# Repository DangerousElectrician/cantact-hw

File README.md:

I need a sensor node that sits on a CAN bus. This looks like a good place to start.

# CANtact Hardware

This repository contains the hardware design files for the CANtact tool. They 
can be opened and edited with [KiCad](http://www.kicad-pcb.org/).

A PDF of the schematic is available
[here](https://github.com/CANtact/cantact-hw/blob/master/cantact.pdf?raw=true).

## License

Hardware files released under the [Creative Commons Attribution-ShareAlike 4.0
International License](http://creativecommons.org/licenses/by-sa/4.0/) (CC BY-SA
4.0)

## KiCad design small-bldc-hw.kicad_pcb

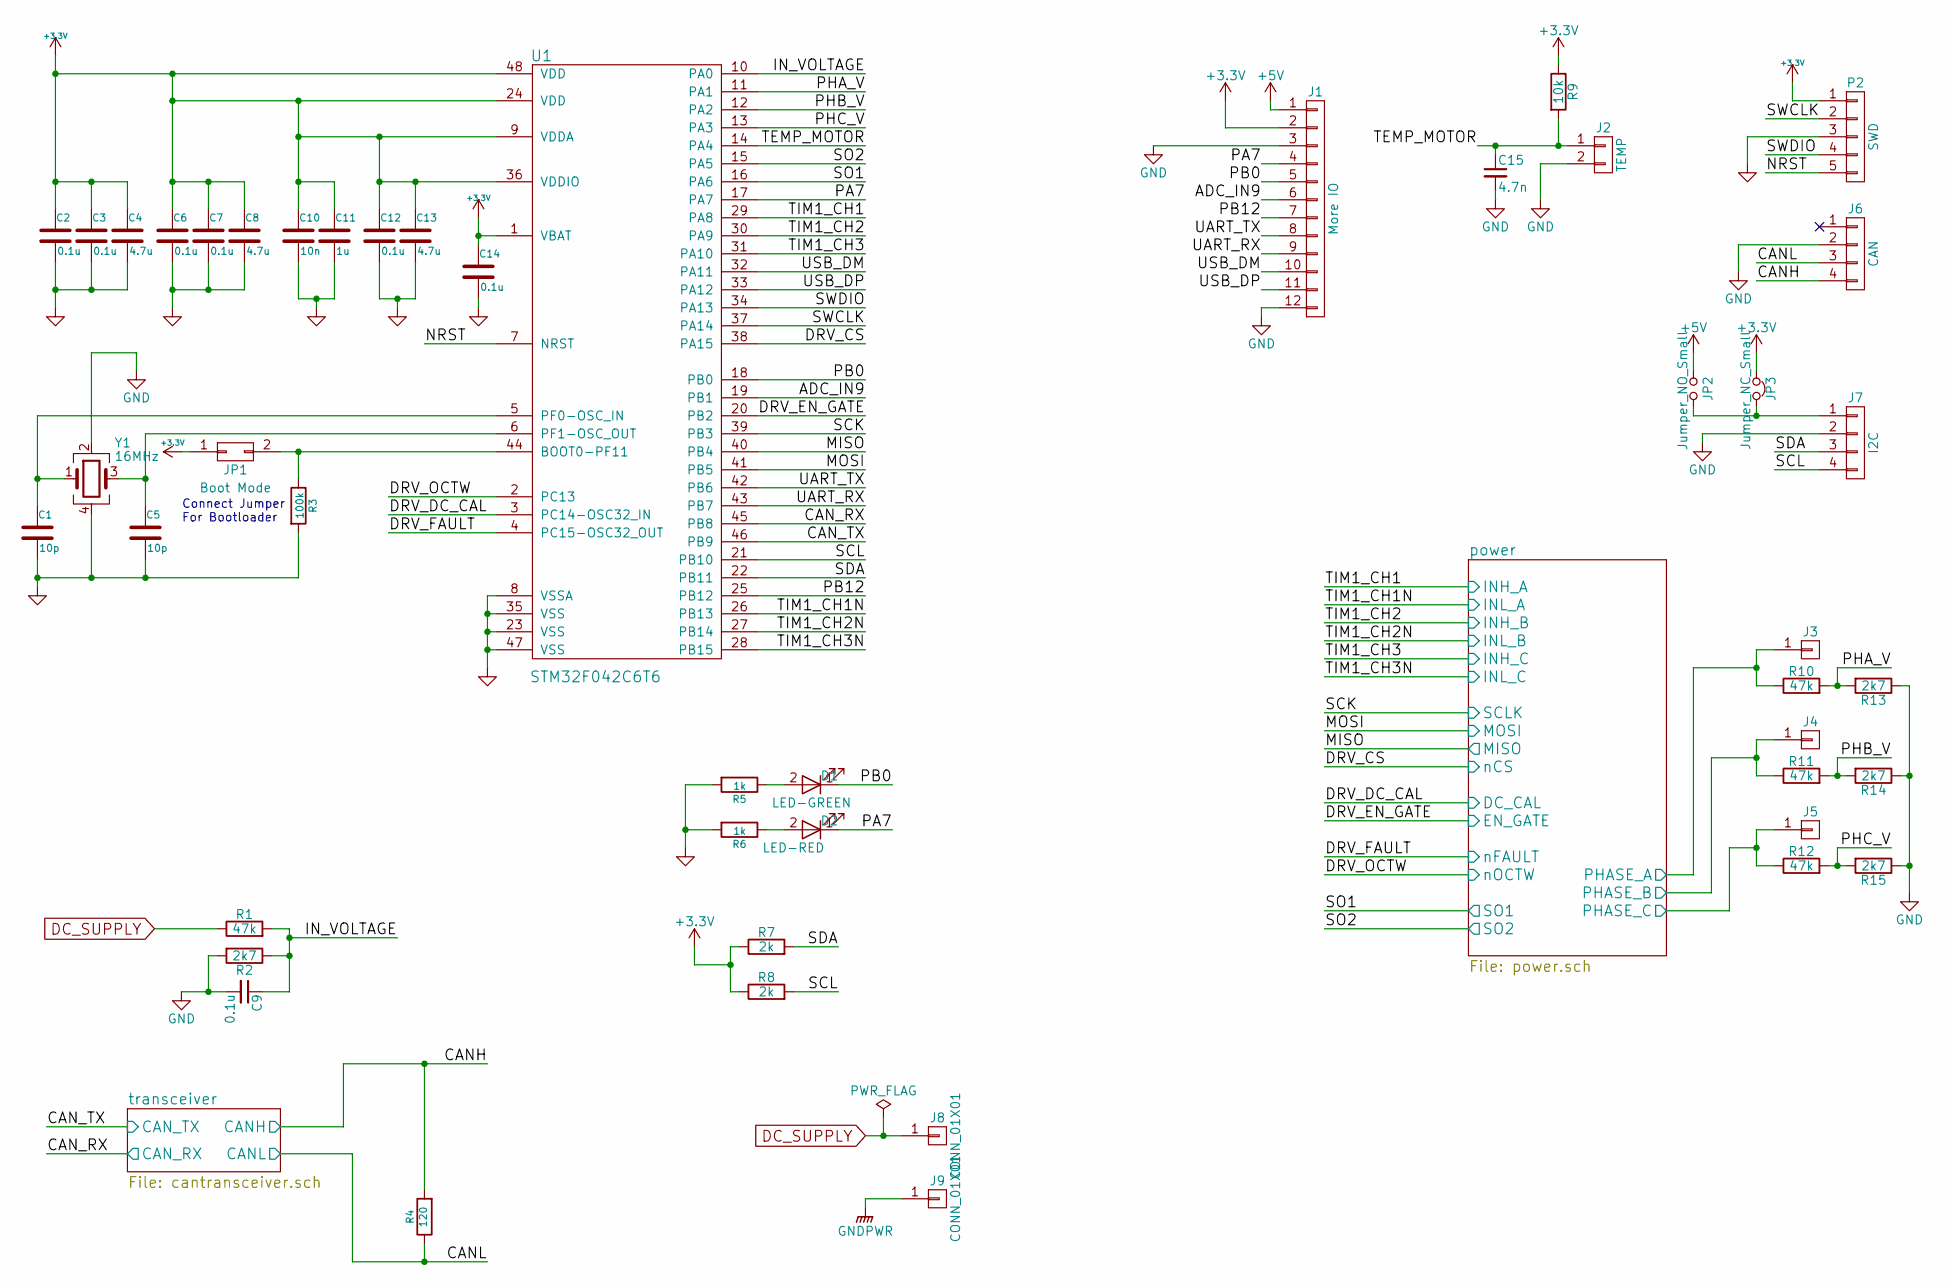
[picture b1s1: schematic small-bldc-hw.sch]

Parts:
C1, C5: 10p; C_0201; MPN GRM0335C1H100JA01D
C2, C9: 0.1u; C_0402; MPN CL05A104KP5NNNC
C3, C6, C7: 0.1u; C_0402; MPN GRM188R71C104KA01D
C4: 4.7u; C_0603; MPN CL10B475KQ8NQNC
C8, C13: 4.7u; C_0603; MPN GRM188R60J475KE19D
C10: 10n; C_0402; MPN GRM188R71H103KA01D
C11: 1u; C_0402; MPN GRM188R61E105KA12D
C12, C14: 0.1u; C_0402; MPN CL05B104KO5NNNC
C15: 4.7n; C_0201; MPN GRM033R71A472KA01D
D1: LED-GREEN; LED_0603; MPN LTST-C191KGKT
D2: LED-RED; LED_0603; MPN LTST-C191KRKT
J1: More IO; JST_SH_SM12B-SRSS-TB_12x1.00mm_Angled
J2: TEMP; JST_SH_SM02B-SRSS-TB_02x1.00mm_Angled
J3, J4, J5, J8, J9: CONN_01X01; SolderWirePad_single_SMD_5x3.5mm_holes
J6: CAN; JST_SH_SM04B-SRSS-TB_04x1.00mm_Angled
J7: I2C; JST_SH_SM04B-SRSS-TB_04x1.00mm_Angled
JP1: Boot Mode; R_0603_HandSoldering
JP2: Jumper_NO_Small; R_0402
JP3: Jumper_NC_Small; R_0402
P2: SWD; JST_SH_SM05B-SRSS-TB_05x1.00mm_Angled
R1, R10, R11, R12: 47k; R_0603
R2, R13, R14, R15: 2k7; R_0201
R3: 100k; R_0201; MPN MCR03ERTF5100
R4: 120; R_0201; MPN MCR03ERTF1200
R5, R6: 1k; R_0201; MPN MCR03ERTF1200
R7, R8: 2k; R_0402
R9: 10k; R_0201
U1: STM32F042C6T6; LQFP-48_7x7mm_Pitch0.5mm; MPN STM32F042C6T6
Y1: 16MHz; Crystal_SMD_3225-4pin_3.2x2.5mm; MPN FA-238 16.0000MB-K3

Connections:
+3V3: C2.1, C3.1, C4.1, C6.1, C7.1, C8.1, C10.1, C11.1, C12.1, C13.1, C14.1, J1.2, JP1.1, JP3.1, P2.1, R7.1, R8.1, R9.1, U1.1 (VBAT), U1.9 (VDDA), U1.24 (VDD), U1.36 (VDDIO), U1.48 (VDD); also elsewhere on the board
+5V: J1.1, JP2.1; also elsewhere on the board
/ADC_IN9: J1.6, U1.19 (PB1)
/CANH: J6.4, R4.2; also elsewhere on the board
/CANL: J6.3, R4.1; also elsewhere on the board
/CAN_RX: U1.45 (PB8); also elsewhere on the board
/CAN_TX: U1.46 (PB9); also elsewhere on the board
/DRV_CS: U1.38 (PA15); also elsewhere on the board
/DRV_DC_CAL: U1.3 (PC14-OSC32_IN); also elsewhere on the board
/DRV_EN_GATE: U1.20 (PB2); also elsewhere on the board
/DRV_FAULT: U1.4 (PC15-OSC32_OUT); also elsewhere on the board
/DRV_OCTW: U1.2 (PC13); also elsewhere on the board
/IN_VOLTAGE: C9.1, R1.2, R2.1, U1.10 (PA0)
/MISO: U1.40 (PB4); also elsewhere on the board
/MOSI: U1.41 (PB5); also elsewhere on the board
/NRST: P2.5, U1.7 (NRST)
/PA7: D2.1 (K), J1.4, U1.17 (PA7)
/PB0: D1.1 (K), J1.5, U1.18 (PB0)
/PB12: J1.7, U1.25 (PB12)
/PHA_V: R10.2, R13.2, U1.11 (PA1)
/PHB_V: R11.2, R14.2, U1.12 (PA2)
/PHC_V: R12.2, R15.2, U1.13 (PA3)
/SCK: U1.39 (PB3); also elsewhere on the board
/SCL: J7.4, R8.2, U1.21 (PB10)
/SDA: J7.3, R7.2, U1.22 (PB11)
/SO1: U1.16 (PA6); also elsewhere on the board
/SO2: U1.15 (PA5); also elsewhere on the board
/SWCLK: P2.2, U1.37 (PA14)
/SWDIO: P2.4, U1.34 (PA13)
/TEMP_MOTOR: C15.1, J2.1, R9.2, U1.14 (PA4)
/TIM1_CH1: U1.29 (PA8); also elsewhere on the board
/TIM1_CH1N: U1.26 (PB13); also elsewhere on the board
/TIM1_CH2: U1.30 (PA9); also elsewhere on the board
/TIM1_CH2N: U1.27 (PB14); also elsewhere on the board
/TIM1_CH3: U1.31 (PA10); also elsewhere on the board
/TIM1_CH3N: U1.28 (PB15); also elsewhere on the board
/UART_RX: J1.9, U1.43 (PB7)
/UART_TX: J1.8, U1.42 (PB6)
/USB_DM: J1.10, U1.32 (PA11)
/USB_DP: J1.11, U1.33 (PA12)
/power/PHASE_A: J3.1, R10.1; also elsewhere on the board
/power/PHASE_B: J4.1, R11.1; also elsewhere on the board
/power/PHASE_C: J5.1, R12.1; also elsewhere on the board
DC_SUPPLY: J8.1, R1.1; also elsewhere on the board
GND: C1.2, C2.2, C3.2, C4.2, C5.2, C6.2, C7.2, C8.2, C9.2, C10.2, C11.2, C12.2, C13.2, C14.2, C15.2, J1.3, J1.12, J2.2, J6.2, J7.2, P2.3, R2.2, R3.2, R5.2, R6.2, R13.1, R14.1, R15.1, U1.8 (VSSA), U1.23 (VSS), U1.35 (VSS), U1.47 (VSS), Y1.2, Y1.4; also elsewhere on the board
GNDPWR: J9.1; also elsewhere on the board
unnamed: C1.1, U1.5 (PF0-OSC_IN), Y1.1
unnamed: C5.1, U1.6 (PF1-OSC_OUT), Y1.3
unnamed: D1.2 (A), R5.1
unnamed: D2.2 (A), R6.1
unnamed: J7.1, JP2.2, JP3.2
unnamed: JP1.2, R3.1, U1.44 (BOOT0-PF11)

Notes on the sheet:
Connect Jumper For Bootloader

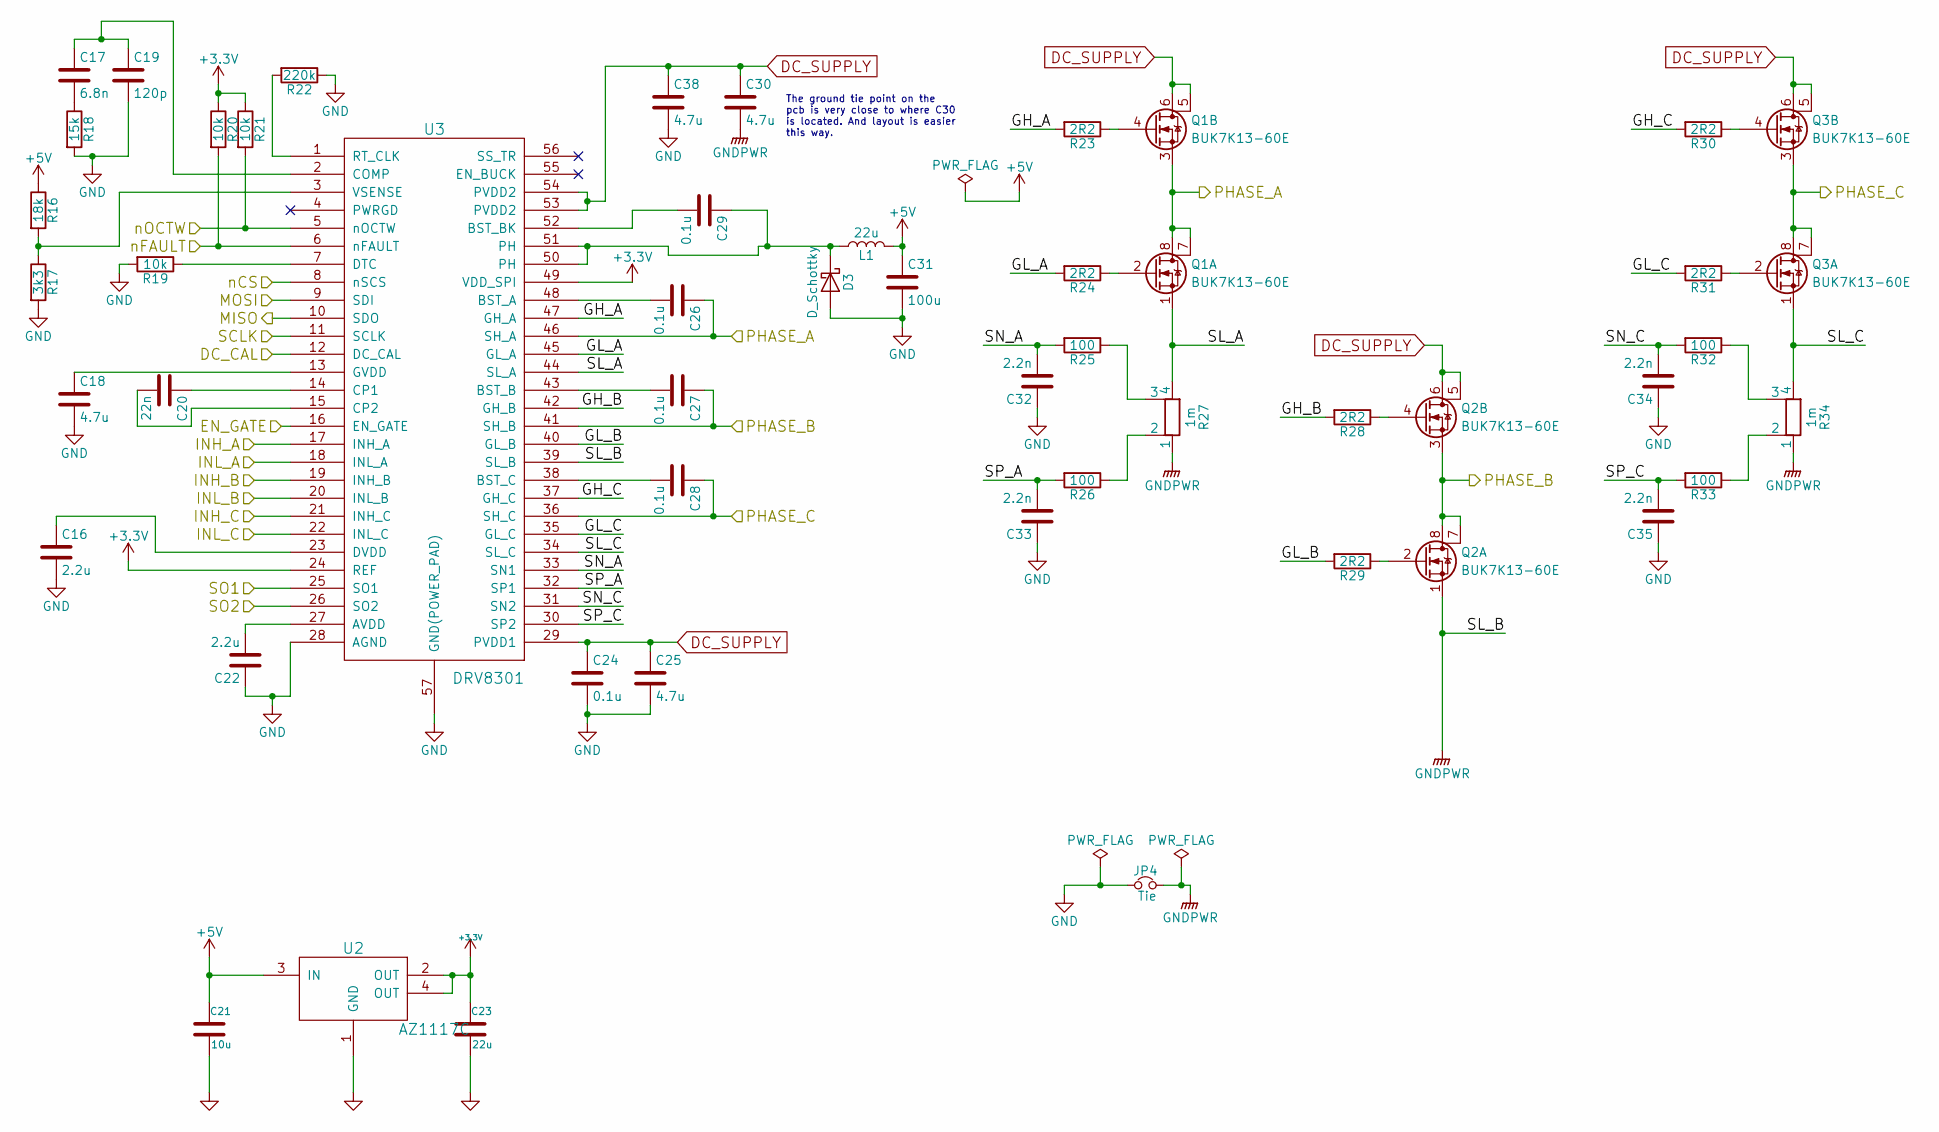
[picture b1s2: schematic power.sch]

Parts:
C16: 2.2u; C_0402; MPN GRM155R61A225KE95D
C17: 6.8n; C_0201; MPN GRM033R71A682KA01D
C18: 4.7u; C_0805; MPN CL21A475KAQNNNG
C19: 120p; C_0201; MPN GRM0335C1H121JA01D
C20: 22n; C_0603; MPN C0603C223K1RACTU
C21: 10u; C_0805; MPN C0805C106K8PACTU
C22: 2.2u; C_0603; MPN CC0603MRX5R7BB225
C23: 22u; C_0805; MPN CL21A226KQCLRNC
C24, C29: 0.1u; C_0805; MPN CL21B104KCFNNNE
C25, C30, C38: 4.7u; C_1210; MPN HMK325BJ475KM-PE
C26, C27, C28: 0.1u; C_0402; MPN GRM155R61E104KA87D
C31: 100u; C_1206; MPN GRM31CR60J107ME39L
C32: 2.2n; C_0201; MPN GRM033R71A222KA01D
C33, C34, C35: 2.2n; C_0201
D3: D_Schottky; D_SOD-123F; MPN NRVTS260ESFT1G
JP4: Tie; NetTie-I_Connected_SMD
L1: 22u; Inductor_Taiyo-Yuden_NR-60xx; MPN NR6045T220M
Q1, Q2, Q3: BUK7K13-60E; SOT-1205
R16: 18k; R_0201
R17: 3k3; R_0201
R18: 15k; R_0201
R19, R20, R21: 10k; R_0201
R22: 220k; R_0201
R23, R24, R28, R29, R30, R31: 2R2; R_0402
R25, R26, R32, R33: 100; R_0201
R27, R34: 1m; R_shunt_4_terminal_2512
U2: AZ1117C; SOT89-3_Housing; MPN AZ1117CR-3.3TRG1
U3: DRV8301; TSSOP-56-PP

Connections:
+3V3: C23.1, R20.1, R21.1, U2.2 (OUT), U2.4 (OUT), U3.24 (REF), U3.49 (VDD_SPI); also elsewhere on the board
+5V: C21.1, C31.1, L1.2, R16.1, U2.3 (IN); also elsewhere on the board
/DRV_CS: U3.8 (nSCS); also elsewhere on the board
/DRV_DC_CAL: U3.12 (DC_CAL); also elsewhere on the board
/DRV_EN_GATE: U3.16 (EN_GATE); also elsewhere on the board
/DRV_FAULT: R20.2, U3.6 (nFAULT); also elsewhere on the board
/DRV_OCTW: R21.2, U3.5 (nOCTW); also elsewhere on the board
/MISO: U3.10 (SDO); also elsewhere on the board
/MOSI: U3.9 (SDI); also elsewhere on the board
/SCK: U3.11 (SCLK); also elsewhere on the board
/SO1: U3.25 (SO1); also elsewhere on the board
/SO2: U3.26 (SO2); also elsewhere on the board
/TIM1_CH1: U3.17 (INH_A); also elsewhere on the board
/TIM1_CH1N: U3.18 (INL_A); also elsewhere on the board
/TIM1_CH2: U3.19 (INH_B); also elsewhere on the board
/TIM1_CH2N: U3.20 (INL_B); also elsewhere on the board
/TIM1_CH3: U3.21 (INH_C); also elsewhere on the board
/TIM1_CH3N: U3.22 (INL_C); also elsewhere on the board
/power/GH_A: R23.2, U3.47 (GH_A)
/power/GH_B: R28.2, U3.42 (GH_B)
/power/GH_C: R30.2, U3.37 (GH_C)
/power/GL_A: R24.2, U3.45 (GL_A)
/power/GL_B: R29.2, U3.40 (GL_B)
/power/GL_C: R31.2, U3.35 (GL_C)
/power/PHASE_A: C26.1, Q1.3 (S), Q1.7 (D), Q1.8 (D), U3.46 (SH_A); also elsewhere on the board
/power/PHASE_B: C27.1, Q2.3 (S), Q2.7 (D), Q2.8 (D), U3.41 (SH_B); also elsewhere on the board
/power/PHASE_C: C28.1, Q3.3 (S), Q3.7 (D), Q3.8 (D), U3.36 (SH_C); also elsewhere on the board
/power/SL_A: Q1.1 (S), R27.4, U3.44 (SL_A)
/power/SL_C: Q3.1 (S), R34.4, U3.34 (SL_C)
/power/SN_A: C32.2, R25.2, U3.33 (SN1)
/power/SN_C: C34.2, R32.2, U3.31 (SN2)
/power/SP_A: C33.2, R26.2, U3.32 (SP1)
/power/SP_C: C35.2, R33.2, U3.30 (SP2)
DC_SUPPLY: C24.1, C25.1, C30.1, C38.1, Q1.5 (D), Q1.6 (D), Q2.5 (D), Q2.6 (D), Q3.5 (D), Q3.6 (D), U3.29 (PVDD1), U3.53 (PVDD2), U3.54 (PVDD2); also elsewhere on the board
GND: C16.2, C18.2, C19.2, C21.2, C22.1, C23.2, C24.2, C25.2, C31.2, C32.1, C33.1, C34.1, C35.1, C38.2, D3.2 (A), JP4.1, R17.2, R18.2, R19.2, R22.1, U2.1 (GND), U3.28 (AGND), U3.57 (GND(POWER_PAD)); also elsewhere on the board
GNDPWR: C30.2, JP4.2, Q2.1 (S), R27.1, R34.1, U3.39 (SL_B); also elsewhere on the board
unnamed: C16.1, U3.23 (DVDD)
unnamed: C17.1, C19.1, U3.2 (COMP)
unnamed: C17.2, R18.1
unnamed: C18.1, U3.13 (GVDD)
unnamed: C20.1, U3.14 (CP1)
unnamed: C20.2, U3.15 (CP2)
unnamed: C22.2, U3.27 (AVDD)
unnamed: C26.2, U3.48 (BST_A)
unnamed: C27.2, U3.43 (BST_B)
unnamed: C28.2, U3.38 (BST_C)
unnamed: C29.1, D3.1 (K), L1.1, U3.50 (PH), U3.51 (PH)
unnamed: C29.2, U3.52 (BST_BK)
unnamed: Q1.2 (G), R24.1
unnamed: Q1.4 (G), R23.1
unnamed: Q2.2 (G), R29.1
unnamed: Q2.4 (G), R28.1
unnamed: Q3.2 (G), R31.1
unnamed: Q3.4 (G), R30.1
unnamed: R16.2, R17.1, U3.3 (VSENSE)
unnamed: R19.1, U3.7 (DTC)
unnamed: R22.2, U3.1 (RT_CLK)
unnamed: R25.1, R27.3
unnamed: R26.1, R27.2
unnamed: R32.1, R34.3
unnamed: R33.1, R34.2

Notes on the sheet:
The ground tie point on the pcb is very close to where C30 is located. And layout is easier this way.

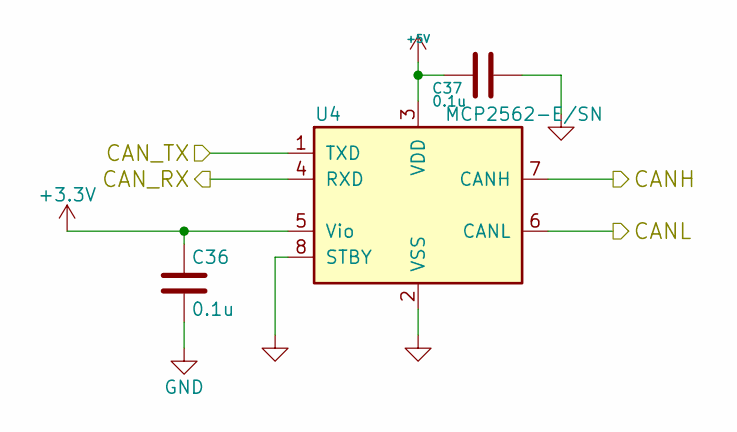
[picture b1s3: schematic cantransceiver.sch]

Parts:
C36: 0.1u; C_0402; MPN CL05B104KO5NNNC
C37: 0.1u; C_0402
U4: MCP2562-E/SN; SOIC-8_3.9x4.9mm_Pitch1.27mm

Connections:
+3V3: C36.1, U4.5 (Vio); also elsewhere on the board
+5V: C37.2, U4.3 (VDD); also elsewhere on the board
/CANH: U4.7 (CANH); also elsewhere on the board
/CANL: U4.6 (CANL); also elsewhere on the board
/CAN_RX: U4.4 (RXD); also elsewhere on the board
/CAN_TX: U4.1 (TXD); also elsewhere on the board
GND: C36.2, C37.1, U4.2 (VSS), U4.8 (STBY); also elsewhere on the board

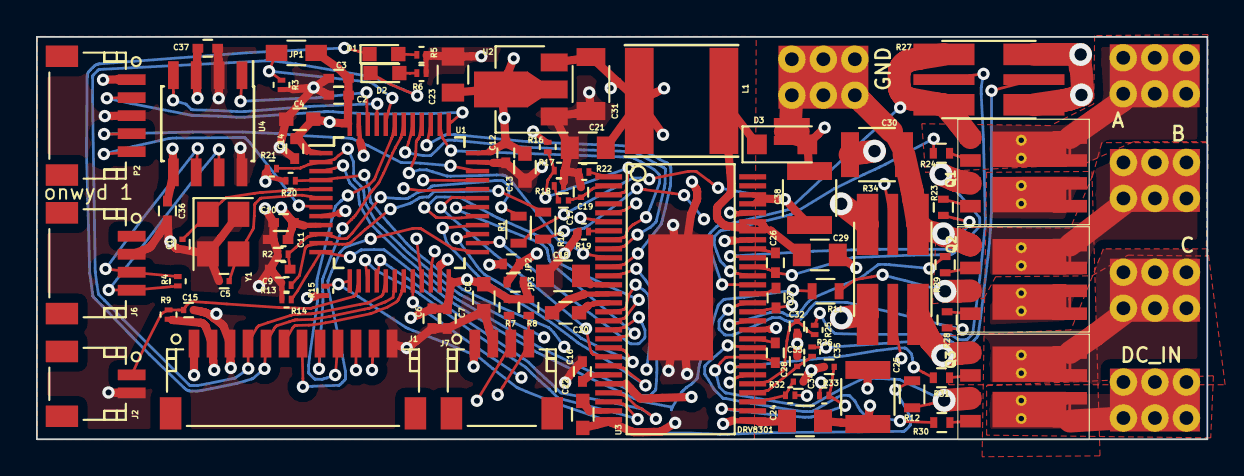
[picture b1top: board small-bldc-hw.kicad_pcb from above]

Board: 4 copper layers, 65.0 x 22.4 mm, 98 parts (0 on the bottom side), 89 nets.

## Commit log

2017-03-20 read in the old schematic and reconnect all the changed symbols
2017-03-20 ignore bak
2017-07-23 cleaning up
2017-07-23 changes of some sort
2017-08-03 stuff
2017-08-05 board design
2017-08-07 routed parts of the power section
2017-08-10 cleanup
2017-08-10 all the other stuff lying around but not committed yet, includes freerouting files
2017-08-10 rerouted a trace
2017-08-10 added additional ground via to drv8301 and fixed broken redundant trace
2017-08-10 fixed via drill size
2017-08-10 1 more layer to plane
2017-08-10 all planes done
2017-08-10 silkscreen references moved
2017-08-10 BOM stuff
2017-08-11 update mpn
2017-08-11 labelled the pads
2017-09-07 I think something relating to planes was changed
2017-09-07 someone elses script to generate assembly drawings
2017-09-07 assembly drawing
2017-09-08 utility scripts for kicad
2017-09-08 assembly_references
2017-09-08 clean up
